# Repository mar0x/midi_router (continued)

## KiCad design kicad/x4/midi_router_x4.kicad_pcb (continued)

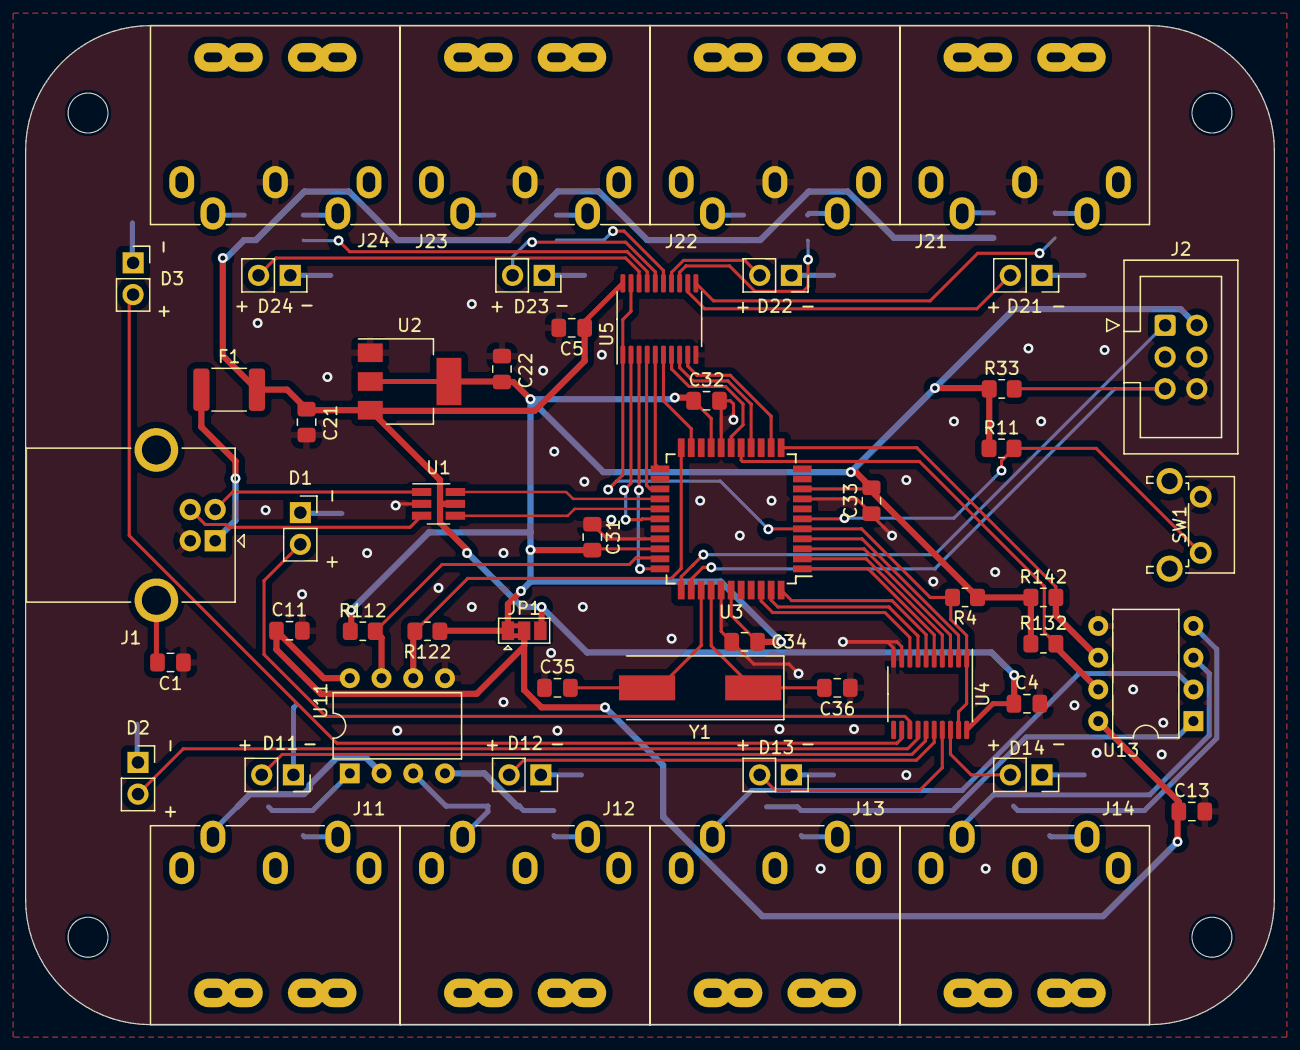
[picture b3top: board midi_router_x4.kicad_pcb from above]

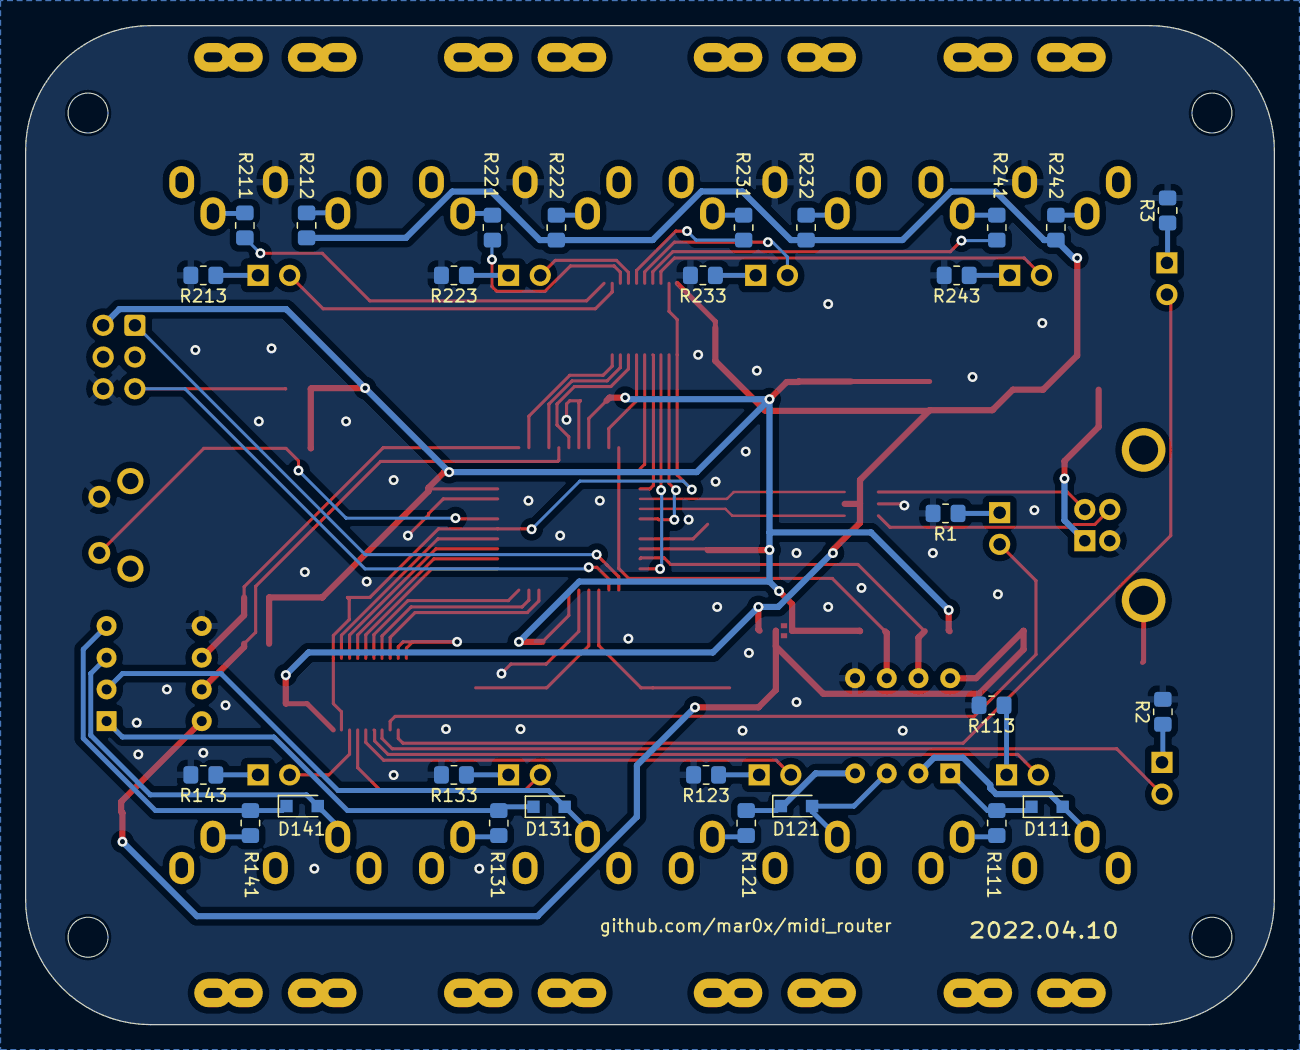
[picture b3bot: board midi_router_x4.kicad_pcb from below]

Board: 2 copper layers, 100.0 x 80.0 mm, 83 parts (27 on the bottom side), 81 nets.

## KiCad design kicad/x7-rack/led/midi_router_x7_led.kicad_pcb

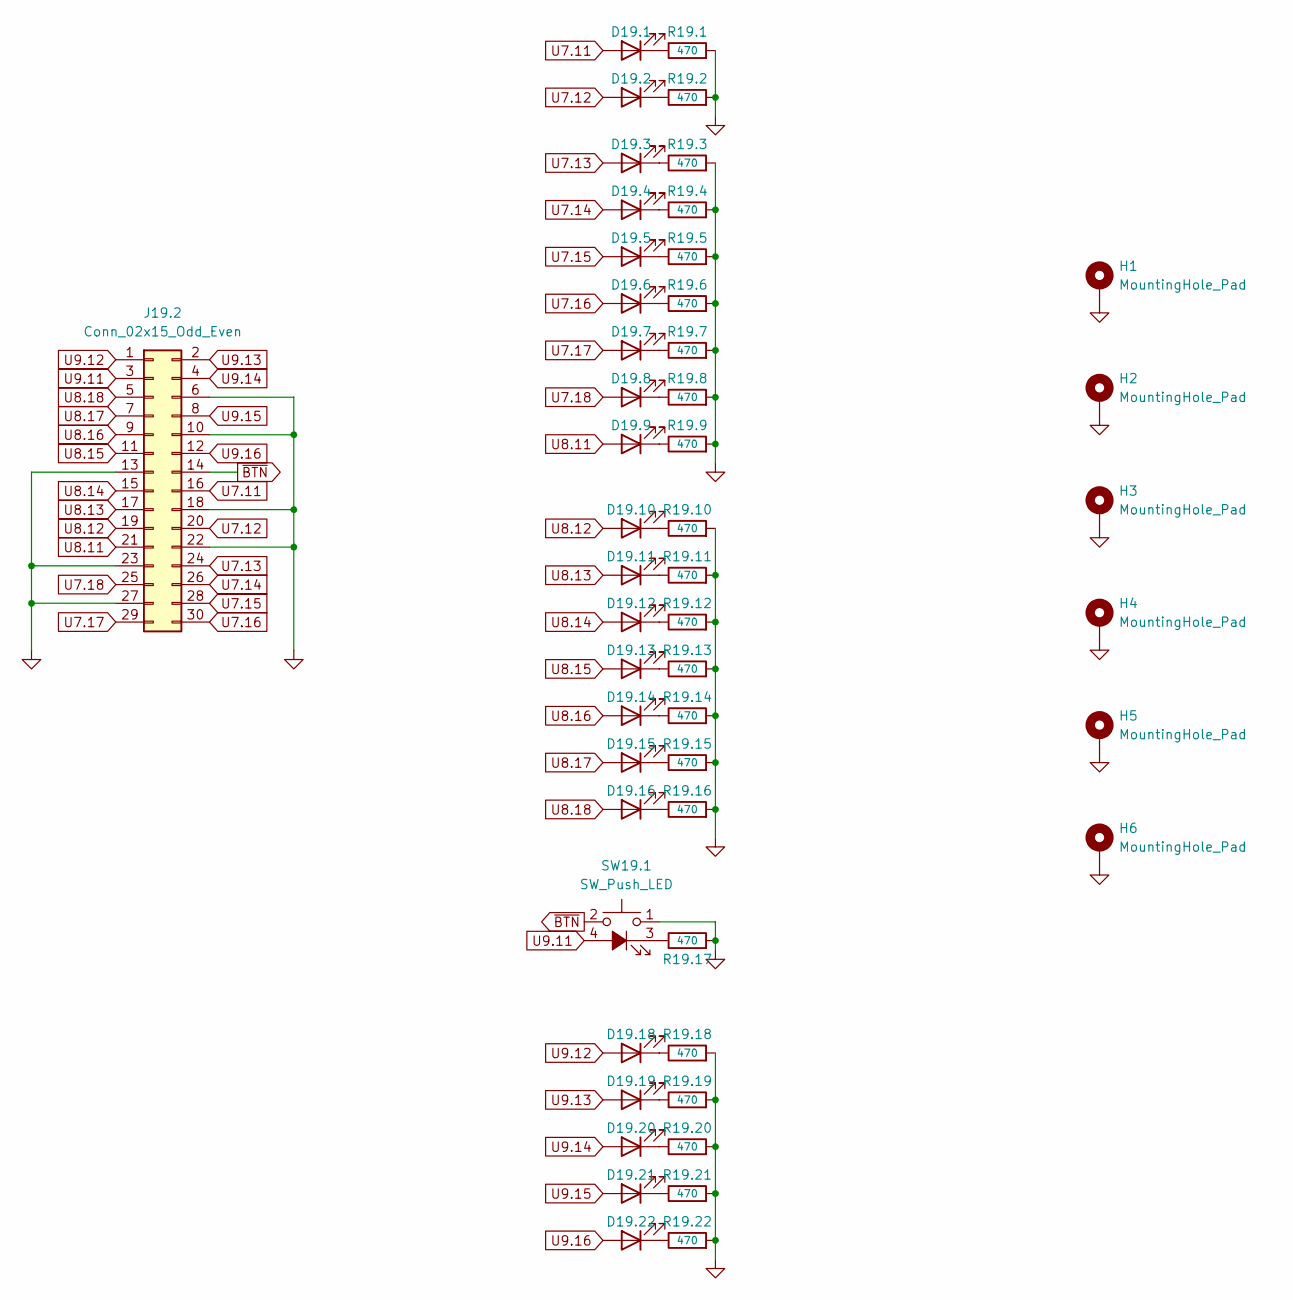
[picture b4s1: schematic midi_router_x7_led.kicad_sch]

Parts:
D19.1, D19.2, D19.3, D19.4, D19.5, D19.6, D19.7, D19.8, D19.9, D19.10, D19.11, D19.12, D19.13, D19.14, D19.15, D19.16, D19.18, D19.19, D19.20, D19.21, D19.22: LED; LED_Rectangular_W5.0mm_H2.0mm
H1, H2, H3, H4, H5, H6: MountingHole_Pad; MountingHole_3.2mm_M3_Pad_Via
J19.2: Conn_02x15_Odd_Even; IDC-Header_2x15_P2.54mm_Vertical
R19.1, R19.2, R19.3, R19.4, R19.5, R19.6, R19.7, R19.8, R19.9, R19.10, R19.11, R19.12, R19.13, R19.14, R19.15, R19.16, R19.17, R19.18, R19.19, R19.20, R19.21, R19.22: 470; R_0805_2012Metric
SW19.1: SW_Push_LED; SW_PUSH_6mm

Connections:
GND: H1.1, H2.1, H3.1, H4.1, H5.1, H6.1, J19.2.6, J19.2.10, J19.2.13, J19.2.18, J19.2.22, J19.2.23, J19.2.27, R19.1.2, R19.2.2, R19.3.2, R19.4.2, R19.5.2, R19.6.2, R19.7.2, R19.8.2, R19.9.2, R19.10.2, R19.11.2, R19.12.2, R19.13.2, R19.14.2, R19.15.2, R19.16.2, R19.17.2, R19.18.2, R19.19.2, R19.20.2, R19.21.2, R19.22.2, SW19.1.1
unnamed: D19.1.1 (K), R19.1.1
unnamed: D19.2.1 (K), R19.2.1
unnamed: D19.3.1 (K), R19.3.1
unnamed: D19.4.1 (K), R19.4.1
unnamed: D19.5.1 (K), R19.5.1
unnamed: D19.6.1 (K), R19.6.1
unnamed: D19.7.1 (K), R19.7.1
unnamed: D19.8.1 (K), R19.8.1
unnamed: D19.9.1 (K), R19.9.1
unnamed: D19.10.1 (K), R19.10.1
unnamed: D19.11.1 (K), R19.11.1
unnamed: D19.12.1 (K), R19.12.1
unnamed: D19.13.1 (K), R19.13.1
unnamed: D19.14.1 (K), R19.14.1
unnamed: D19.15.1 (K), R19.15.1
unnamed: D19.16.1 (K), R19.16.1
unnamed: D19.18.1 (K), R19.18.1
unnamed: D19.19.1 (K), R19.19.1
unnamed: D19.20.1 (K), R19.20.1
unnamed: D19.21.1 (K), R19.21.1
unnamed: D19.22.1 (K), R19.22.1
unnamed: R19.17.1, SW19.1.3 (K)
U7.11: D19.1.2 (A), J19.2.16
U7.12: D19.2.2 (A), J19.2.20
U7.13: D19.3.2 (A), J19.2.24
U7.14: D19.4.2 (A), J19.2.26
U7.15: D19.5.2 (A), J19.2.28
U7.16: D19.6.2 (A), J19.2.30
U7.17: D19.7.2 (A), J19.2.29
U7.18: D19.8.2 (A), J19.2.25
U8.11: D19.9.2 (A), J19.2.21
U8.12: D19.10.2 (A), J19.2.19
U8.13: D19.11.2 (A), J19.2.17
U8.14: D19.12.2 (A), J19.2.15
U8.15: D19.13.2 (A), J19.2.11
U8.16: D19.14.2 (A), J19.2.9
U8.17: D19.15.2 (A), J19.2.7
U8.18: D19.16.2 (A), J19.2.5
U9.11: J19.2.3, SW19.1.4 (A)
U9.12: D19.18.2 (A), J19.2.1
U9.13: D19.19.2 (A), J19.2.2
U9.14: D19.20.2 (A), J19.2.4
U9.15: D19.21.2 (A), J19.2.8
U9.16: D19.22.2 (A), J19.2.12
~BTN: J19.2.14, SW19.1.2

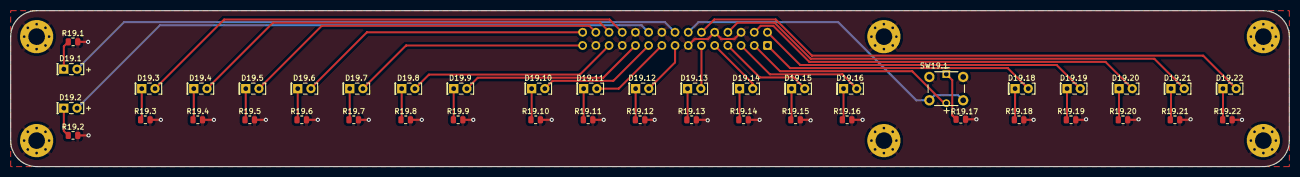
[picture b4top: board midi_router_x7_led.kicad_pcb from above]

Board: 2 copper layers, 246.0 x 30.0 mm, 51 parts (1 on the bottom side), 46 nets.

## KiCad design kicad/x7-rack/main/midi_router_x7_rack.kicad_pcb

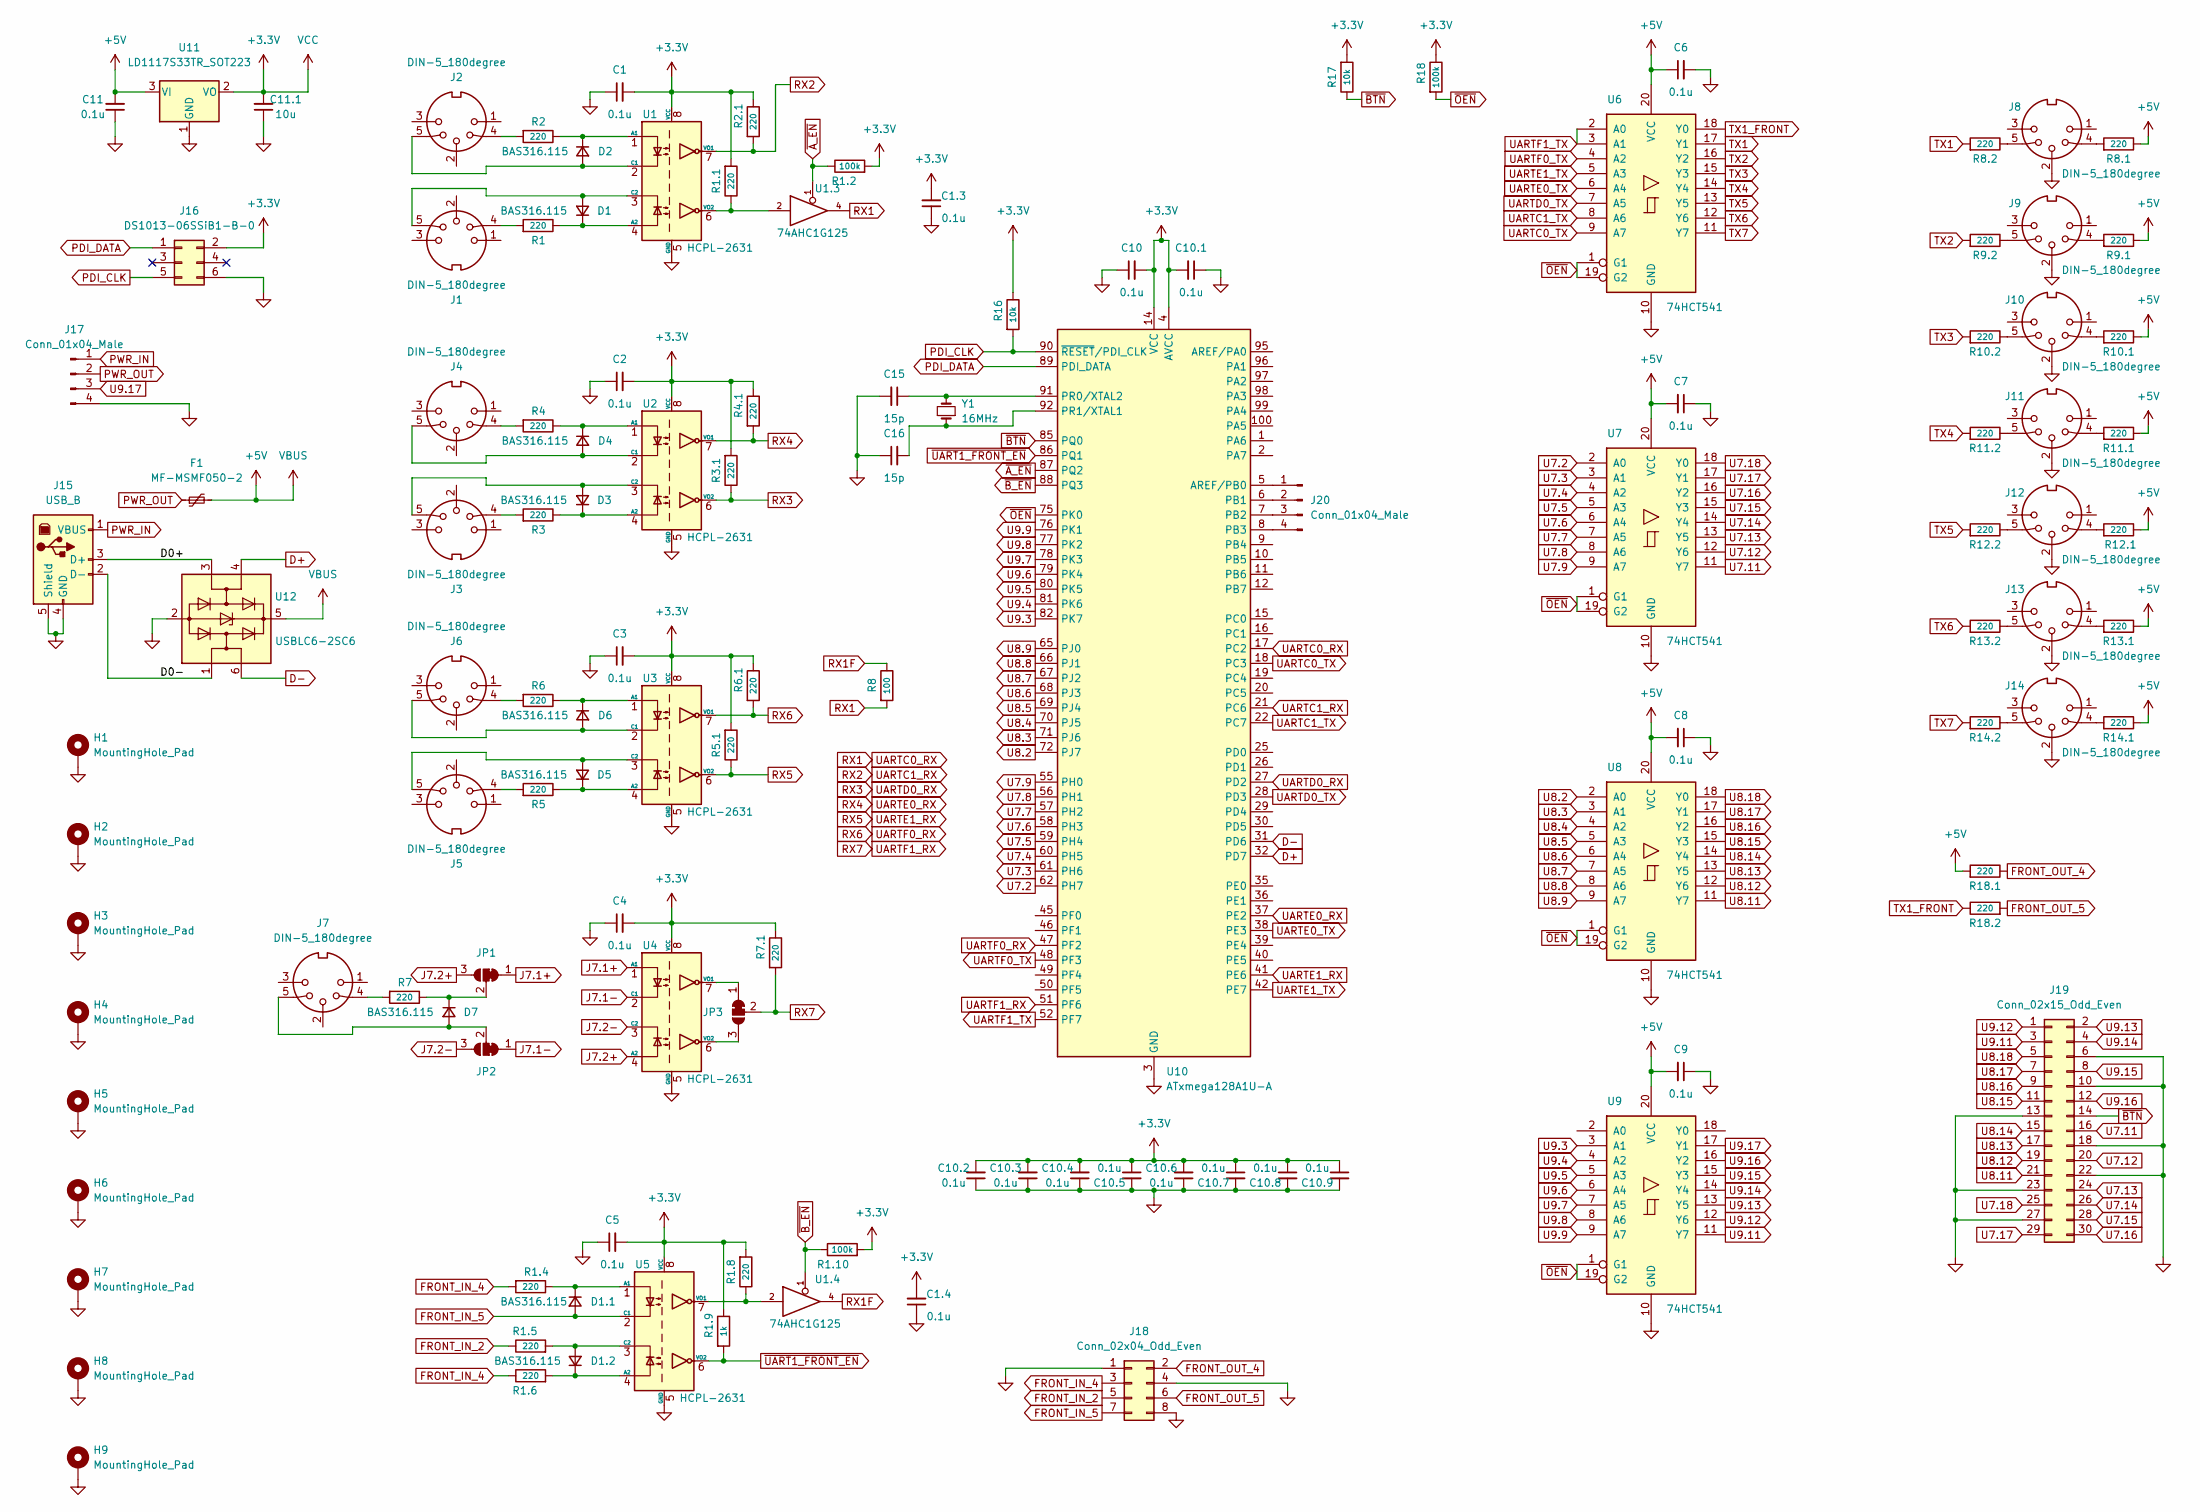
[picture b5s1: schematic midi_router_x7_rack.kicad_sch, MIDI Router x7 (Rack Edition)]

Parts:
C1, C1.3, C1.4, C2, C3, C4, C5, C6, C7, C8, C9, C10, C10.1, C10.2, C10.3, C10.4, C10.5, C10.6, C10.7, C10.8, C10.9, C11: 0.1u; C_0805_2012Metric
C11.1: 10u; C_0805_2012Metric
C15, C16: 15p; C_0805_2012Metric
D1, D1.1, D1.2, D2, D3, D4, D5, D6, D7: BAS316.115; D_SOD-323_HandSoldering
F1: MF-MSMF050-2; Fuse_1812_4532Metric
H1, H2, H3, H4, H5, H6, H7, H8, H9: MountingHole_Pad; MountingHole_3.2mm_M3_Pad_Via
J1, J2, J3, J4, J5, J6, J7, J8, J9, J10, J11, J12, J13, J14: DIN-5_180degree; DIN5MIDI-OOTDTY
J15: USB_B; USB_B_OST_USB-B1HSxx_Horizontal
J16: DS1013-06SSiB1-B-0; IDC-Header_2x03_P2.54mm_Vertical
J17: Conn_01x04_Male; JST_EH_B4B-EH-A_1x04_P2.50mm_Vertical
J18: Conn_02x04_Odd_Even; IDC-Header_2x04_P2.54mm_Vertical
J19: Conn_02x15_Odd_Even; IDC-Header_2x15_P2.54mm_Vertical
J20: Conn_01x04_Male; PinHeader_1x04_P2.54mm_Vertical
JP1, JP2, JP3: SolderJumper_3_Bridged12; SolderJumper-3_P1.3mm_Bridged12_RoundedPad1.0x1.5mm_NumberL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
R1, R1.1, R1.4, R1.5, R1.6, R1.8, R2, R2.1, R3, R3.1, R4, R4.1, R5, R5.1, R6, R6.1, R7, R7.1, R8.1, R8.2, R9.1, R9.2, R10.1, R10.2, R11.1, R11.2, R12.1, R12.2, R13.1, R13.2, R14.1, R14.2, R18.1, R18.2: 220; R_0805_2012Metric
R1.2, R1.10, R18: 100k; R_0805_2012Metric
R1.9: 1k; R_0805_2012Metric
R8: 100; R_0805_2012Metric
R16, R17: 10k; R_0805_2012Metric
U1, U2, U3, U4, U5: HCPL-2631; DIP-8_W7.62mm
U1.3, U1.4: 74AHC1G125; SOT-23-5
U6, U7, U8, U9: 74HCT541; TSSOP-20_4.4x6.5mm_P0.65mm
U10: ATxmega128A1U-A; TQFP-100_14x14mm_P0.5mm
U11: LD1117S33TR_SOT223; SOT-223-3_TabPin2
U12: USBLC6-2SC6; SOT-23-6
Y1: 16MHz; Crystal_SMD_HC49-SD

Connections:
+3V3: C1.2, C1.3.2, C1.4.2, C2.2, C3.2, C4.2, C5.2, C10.2, C10.1.2, C10.2.2, C10.3.2, C10.4.2, C10.5.1, C10.6.2, C10.7.1, C10.8.1, C10.9.1, C11.1.2, J16.2, R1.1.2, R1.2.2, R1.8.2, R1.9.1, R1.10.2, R2.1.1, R3.1.2, R4.1.1, R5.1.2, R6.1.1, R7.1.1, R16.1, R17.2, R18.1, U1.8 (VCC), U1.3.5 (VCC), U1.4.5 (VCC), U2.8 (VCC), U3.8 (VCC), U4.8 (VCC), U5.8 (VCC), U10.4 (AVCC), U10.14 (VCC), U10.24 (VCC), U10.34 (VCC), U10.44 (VCC), U10.54 (VCC), U10.64 (VCC), U10.74 (VCC), U10.83 (VCC), U10.94 (AVCC), U11.2 (VO)
+5V: C6.1, C7.2, C8.2, C9.2, C11.2, F1.2, R8.1.1, R9.1.1, R10.1.1, R11.1.1, R12.1.1, R13.1.1, R14.1.1, R18.1.2, U6.20 (VCC), U7.20 (VCC), U8.20 (VCC), U9.20 (VCC), U11.3 (VI), U12.5 (VBUS)
/D0+: J15.3 (D+), U12.3 (I/O2)
/D0-: J15.2 (D-), U12.1 (I/O1)
D+: U10.32 (PD7), U12.4 (I/O2)
D-: U10.31 (PD6), U12.6 (I/O1)
FRONT_IN_2: J18.5, R1.5.1
FRONT_IN_4: J18.3, R1.4.2, R1.6.1
FRONT_IN_5: D1.1.2 (A), J18.7, U5.2 (C1)
FRONT_OUT_4: J18.2, R18.1.1
FRONT_OUT_5: J18.6, R18.2.2
GND: C1.1, C1.3.1, C1.4.1, C2.1, C3.1, C4.1, C5.1, C6.2, C7.1, C8.1, C9.1, C10.1, C10.1.1, C10.2.1, C10.3.1, C10.4.1, C10.5.2, C10.6.1, C10.7.2, C10.8.2, C10.9.2, C11.1, C11.1.1, C15.2, C16.1, H1.1, H2.1, H3.1, H4.1, H5.1, H6.1, H7.1, H8.1, H9.1, J8.2, J9.2, J10.2, J11.2, J12.2, J13.2, J14.2, J15.4 (GND), J15.5 (Shield), J16.6, J17.4, J18.1, J18.4, J18.8, J19.6, J19.10, J19.13, J19.18, J19.22, J19.23, J19.27, U1.5 (GND), U1.3.3 (GND), U1.4.3 (GND), U2.5 (GND), U3.5 (GND), U4.5 (GND), U5.5 (GND), U6.10 (GND), U7.10 (GND), U8.10 (GND), U9.10 (GND), U10.3 (GND), U10.13 (GND), U10.23 (GND), U10.33 (GND), U10.43 (GND), U10.53 (GND), U10.63 (GND), U10.73 (GND), U10.84 (GND), U10.93 (GND), U11.1 (GND), U12.2 (GND)
J7.1+: JP1.1 (A), U4.1 (A1)
J7.1-: JP2.1 (A), U4.2 (C1)
J7.2+: JP1.3 (B), U4.4 (A2)
J7.2-: JP2.3 (B), U4.3 (C2)
unnamed: D1.2 (A), J1.5, U1.3 (C2)
unnamed: D1.1 (K), R1.1, U1.4 (A2)
unnamed: D1.1.1 (K), R1.4.1, U5.1 (A1)
unnamed: D1.2.2 (A), R1.5.2, U5.3 (C2)
unnamed: D1.2.1 (K), R1.6.2, U5.4 (A2)
unnamed: D2.2 (A), J2.5, U1.2 (C1)
unnamed: D2.1 (K), R2.1, U1.1 (A1)
unnamed: D3.2 (A), J3.5, U2.3 (C2)
unnamed: D3.1 (K), R3.1, U2.4 (A2)
unnamed: D4.2 (A), J4.5, U2.2 (C1)
unnamed: D4.1 (K), R4.1, U2.1 (A1)
unnamed: D5.2 (A), J5.5, U3.3 (C2)
unnamed: D5.1 (K), R5.1, U3.4 (A2)
unnamed: D6.2 (A), J6.5, U3.2 (C1)
unnamed: D6.1 (K), R6.1, U3.1 (A1)
unnamed: D7.2 (A), J7.5, JP2.2 (C)
unnamed: D7.1 (K), JP1.2 (C), R7.1
unnamed: J1.4, R1.2
unnamed: J2.4, R2.2
unnamed: J3.4, R3.2
unnamed: J4.4, R4.2
unnamed: J5.4, R5.2
unnamed: J6.4, R6.2
unnamed: J7.4, R7.2
unnamed: J8.4, R8.1.2
unnamed: J8.5, R8.2.1
unnamed: J9.4, R9.1.2
unnamed: J9.5, R9.2.1
unnamed: J10.4, R10.1.2
unnamed: J10.5, R10.2.1
unnamed: J11.4, R11.1.2
unnamed: J11.5, R11.2.1
unnamed: J12.4, R12.1.2
unnamed: J12.5, R12.2.1
unnamed: J13.4, R13.1.2
unnamed: J13.5, R13.2.1
unnamed: J14.4, R14.1.2
unnamed: J14.5, R14.2.1
unnamed: J20.1, U10.5 (AREF/PB0)
unnamed: J20.2, U10.6 (PB1)
unnamed: J20.3, U10.7 (PB2)
unnamed: J20.4, U10.8 (PB3)
unnamed: JP3.1 (A), U4.7 (VO1)
unnamed: JP3.3 (B), U4.6 (VO2)
unnamed: R1.1.1, U1.6 (VO2), U1.3.2
unnamed: R1.8.1, U1.4.2, U5.7 (VO1)
unnamed: C15.1, U10.91 (PR0/XTAL2), Y1.2
unnamed: C16.2, U10.92 (PR1/XTAL1), Y1.1
PDI_CLK: J16.5, R16.2, U10.90 (~RESET/PDI_CLK)
PDI_DATA: J16.1, U10.89 (PDI_DATA)
PWR_IN: J15.1 (VBUS), J17.1
PWR_OUT: F1.1, J17.2
RX1: R8.2, U1.3.4, U10.17 (PC2)
RX1F: R8.1, U1.4.4
RX2: R2.1.2, U1.7 (VO1), U10.21 (PC6)
RX3: R3.1.1, U2.6 (VO2), U10.27 (PD2)
RX4: R4.1.2, U2.7 (VO1), U10.37 (PE2)
RX5: R5.1.1, U3.6 (VO2), U10.41 (PE6)
RX6: R6.1.2, U3.7 (VO1), U10.47 (PF2)
RX7: JP3.2 (C), R7.1.2, U10.51 (PF6)
TX1: R8.2.2, U6.17 (Y1)
TX1_FRONT: R18.2.1, U6.18 (Y0)
TX2: R9.2.2, U6.16 (Y2)
TX3: R10.2.2, U6.15 (Y3)
TX4: R11.2.2, U6.14 (Y4)
TX5: R12.2.2, U6.13 (Y5)
TX6: R13.2.2, U6.12 (Y6)
TX7: R14.2.2, U6.11 (Y7)
U7.2: U7.2 (A0), U10.62 (PH7)
U7.3: U7.3 (A1), U10.61 (PH6)
U7.4: U7.4 (A2), U10.60 (PH5)
U7.5: U7.5 (A3), U10.59 (PH4)
U7.6: U7.6 (A4), U10.58 (PH3)
U7.7: U7.7 (A5), U10.57 (PH2)
U7.8: U7.8 (A6), U10.56 (PH1)
U7.9: U7.9 (A7), U10.55 (PH0)
U7.11: J19.16, U7.11 (Y7)
U7.12: J19.20, U7.12 (Y6)
U7.13: J19.24, U7.13 (Y5)
U7.14: J19.26, U7.14 (Y4)
U7.15: J19.28, U7.15 (Y3)
U7.16: J19.30, U7.16 (Y2)
U7.17: J19.29, U7.17 (Y1)
U7.18: J19.25, U7.18 (Y0)
U8.2: U8.2 (A0), U10.72 (PJ7)
U8.3: U8.3 (A1), U10.71 (PJ6)
U8.4: U8.4 (A2), U10.70 (PJ5)
U8.5: U8.5 (A3), U10.69 (PJ4)
U8.6: U8.6 (A4), U10.68 (PJ3)
U8.7: U8.7 (A5), U10.67 (PJ2)
U8.8: U8.8 (A6), U10.66 (PJ1)
U8.9: U8.9 (A7), U10.65 (PJ0)
U8.11: J19.21, U8.11 (Y7)
U8.12: J19.19, U8.12 (Y6)
U8.13: J19.17, U8.13 (Y5)
U8.14: J19.15, U8.14 (Y4)
U8.15: J19.11, U8.15 (Y3)
U8.16: J19.9, U8.16 (Y2)
U8.17: J19.7, U8.17 (Y1)
U8.18: J19.5, U8.18 (Y0)
U9.3: U9.3 (A1), U10.82 (PK7)
U9.4: U9.4 (A2), U10.81 (PK6)
U9.5: U9.5 (A3), U10.80 (PK5)
U9.6: U9.6 (A4), U10.79 (PK4)
U9.7: U9.7 (A5), U10.78 (PK3)
U9.8: U9.8 (A6), U10.77 (PK2)
U9.9: U9.9 (A7), U10.76 (PK1)
U9.11: J19.3, U9.11 (Y7)
U9.12: J19.1, U9.12 (Y6)
U9.13: J19.2, U9.13 (Y5)
U9.14: J19.4, U9.14 (Y4)
U9.15: J19.8, U9.15 (Y3)
U9.16: J19.12, U9.16 (Y2)
U9.17: J17.3, U9.17 (Y1)
UARTC0_TX: U6.9 (A7), U10.18 (PC3)
UARTC1_TX: U6.8 (A6), U10.22 (PC7)
UARTD0_TX: U6.7 (A5), U10.28 (PD3)
UARTE0_TX: U6.6 (A4), U10.38 (PE3)
UARTE1_TX: U6.5 (A3), U10.42 (PE7)
UARTF0_TX: U6.4 (A2), U10.48 (PF3)
UARTF1_TX: U6.2 (A0), U6.3 (A1), U10.52 (PF7)
~A_EN: R1.2.1, U1.3.1, U10.87 (PQ2)
~BTN: J19.14, R17.1, U10.85 (PQ0)
~B_EN: R1.10.1, U1.4.1, U10.88 (PQ3)
~OEN: R18.2, U6.1 (G1), U6.19 (G2), U7.1 (G1), U7.19 (G2), U8.1 (G1), U8.19 (G2), U9.1 (G1), U9.19 (G2), U10.75 (PK0)
~UART1_FRONT_EN: R1.9.2, U5.6 (VO2), U10.86 (PQ1)

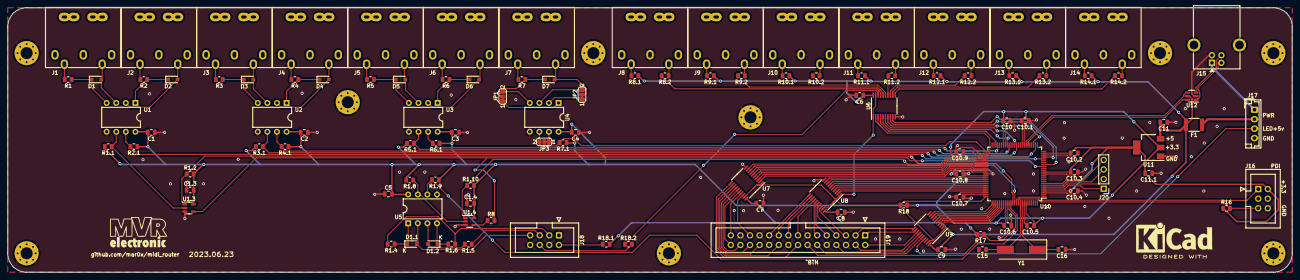
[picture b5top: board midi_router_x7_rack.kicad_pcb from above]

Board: 2 copper layers, 340.0 x 70.0 mm, 123 parts (0 on the bottom side), 142 nets.

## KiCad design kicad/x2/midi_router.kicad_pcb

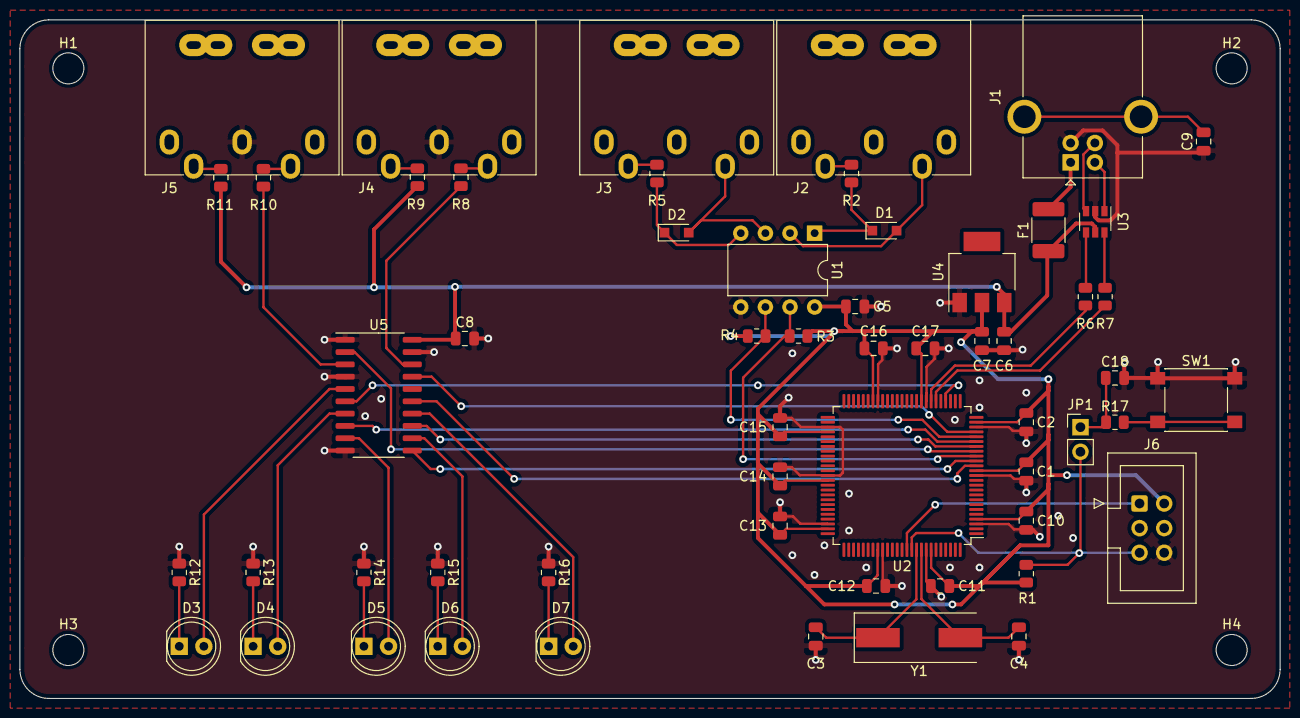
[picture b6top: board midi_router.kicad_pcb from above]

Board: 2 copper layers, 130.0 x 70.0 mm, 61 parts (0 on the bottom side), 48 nets.

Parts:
C1, C2, C5, C6, C8, C10, C11, C12, C13, C14, C15, C16, C17, C18: 0.1u; C_0805_2012Metric
C3, C4: 15p; C_0805_2012Metric
C7: 10u; C_0805_2012Metric
C9: 0.01u; C_0805_2012Metric
D1, D2: D; D_SOD-323_HandSoldering
D3, D4, D5, D6, D7: LED; LED_D5.0mm
F1: MF-MSMF050-2; Fuse_1812_4532Metric_Castellated
H1, H2, H3, H4: MountingHole; MountingHole_3.2mm_M3
J1: USB_B; USB_B_OST_USB-B1HSxx_Horizontal
J2, J3, J4, J5: DIN-5_180degree; DIN5MIDI-OOTDTY
J6: Conn_02x03_Odd_Even; IDC-Header_2x03_P2.54mm_Vertical
JP1: Jumper_NO_Small; PinHeader_1x02_P2.54mm_Vertical
R1: 10k; R_0805_2012Metric
R2, R5, R8, R9, R10, R11: 220; R_0805_2012Metric
R3, R4: 470; R_0805_2012Metric
R6, R7: 22; R_0805_2012Metric
R12, R13, R14, R15, R16: 1k; R_0805_2012Metric
R17: 100; R_0805_2012Metric
SW1: SW_Push; SW_Push_1P1T_NO_6x6mm_H9.5mm
U1: HCPL2730; DIP-8_W7.62mm
U2: ATxmega128A1U-AU; TQFP-100_14x14mm_P0.5mm
U3: USBLC6-2SC6; SOT-23-6
U4: LD1117S33TR_SOT223; SOT-223-3_TabPin2
U5: 74HC244; SO-20_5.3x12.6mm_P1.27mm
Y1: 16MHz; Crystal_SMD_HC49-SD

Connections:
+3V3: C1.2, C2.1, C5.1, C7.1, C10.1, C11.1, C12.1, C13.1, C14.1, C15.1, C16.1, C17.1, J6.2, R1.1, R3.1, R4.1, U1.8, U2.4, U2.14, U2.24, U2.34, U2.44, U2.54, U2.64, U2.74, U2.83, U2.94, U4.2
+5V: C6.1, C8.1, F1.1, R9.1, R11.1, U3.5, U4.3, U5.20
D+: R6.1, U2.32
D-: R7.1, U2.31
GND: C1.1, C2.2, C3.1, C4.1, C5.2, C6.2, C7.2, C8.2, C9.1, C10.2, C11.2, C12.2, C13.2, C14.2, C15.2, C16.2, C17.2, C18.2, J1.4, J4.2, J5.2, J6.6, R12.1, R13.1, R14.1, R15.1, R16.1, SW1.1, U1.5, U2.3, U2.13, U2.23, U2.33, U2.43, U2.53, U2.63, U2.73, U2.84, U2.93, U3.2, U4.1, U5.1, U5.4, U5.10, U5.19
unnamed: C3.2, U2.91, Y1.1
unnamed: C4.2, U2.92, Y1.2
unnamed: C9.2, J1.5
unnamed: C18.1, JP1.1, R17.1
unnamed: D1.1, R2.2, U1.1
unnamed: D1.2, J2.5, U1.2
unnamed: D2.1, R5.2, U1.4
unnamed: D2.2, J3.5, U1.3
unnamed: D3.1, R12.2
unnamed: D3.2, U5.5
unnamed: D4.1, R13.2
unnamed: D4.2, U5.7
unnamed: D5.1, R14.2
unnamed: D5.2, U5.9
unnamed: D6.1, R15.2
unnamed: D6.2, U5.12
unnamed: D7.1, R16.2
unnamed: D7.2, U5.14
unnamed: F1.2, J1.1
unnamed: J1.2, U3.1
unnamed: J1.3, U3.3
unnamed: J2.4, R2.1
unnamed: J3.4, R5.1
unnamed: J4.4, R9.2
unnamed: J4.5, R8.1
unnamed: J5.4, R11.2
unnamed: J5.5, R10.1
unnamed: R6.2, U3.4
unnamed: R7.2, U3.6
unnamed: R8.2, U5.18
unnamed: R10.2, U5.3
unnamed: R17.2, SW1.2
PDI_CLK: J6.5, JP1.2, R1.2, U2.90
PDI_DATA: J6.1, U2.89
UARTC_RXD0: R3.2, U1.7, U2.17
UARTC_RXD1: R4.2, U1.6, U2.21
UARTC_SRX0: U2.15, U5.15
UARTC_SRX1: U2.19, U5.13
UARTC_STX0: U2.16, U5.11
UARTC_STX1: U2.20, U5.8
UARTC_TXD0: U2.18, U5.2
UARTC_TXD1: U2.22, U5.17
UARTD_SUSB: U2.29, U5.6

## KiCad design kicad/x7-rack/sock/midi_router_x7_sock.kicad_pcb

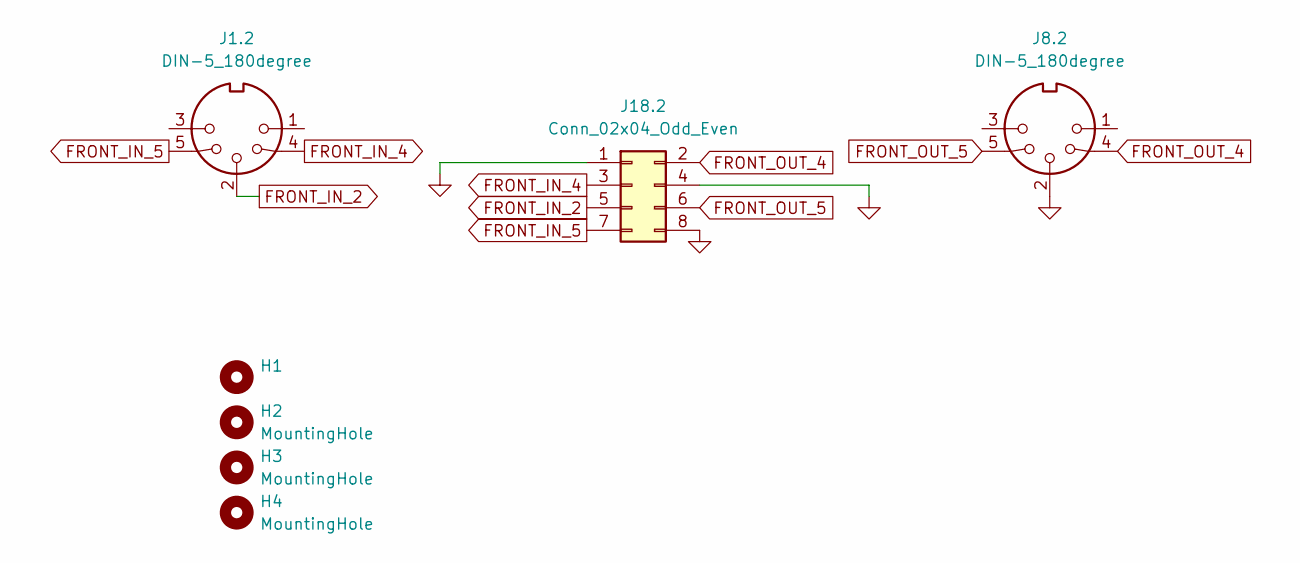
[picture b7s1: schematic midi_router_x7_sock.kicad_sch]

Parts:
H1: (no value)
H2, H3, H4: MountingHole; MountingHole_3.2mm_M3
J1.2, J8.2: DIN-5_180degree; DIN5MIDI-OOTDTY
J18.2: Conn_02x04_Odd_Even; IDC-Header_2x04_P2.54mm_Vertical

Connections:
FRONT_IN_2: J1.2.2, J18.2.5
FRONT_IN_4: J1.2.4, J18.2.3
FRONT_IN_5: J1.2.5, J18.2.7
FRONT_OUT_4: J8.2.4, J18.2.2
FRONT_OUT_5: J8.2.5, J18.2.6
GND: J8.2.2, J18.2.1, J18.2.4, J18.2.8

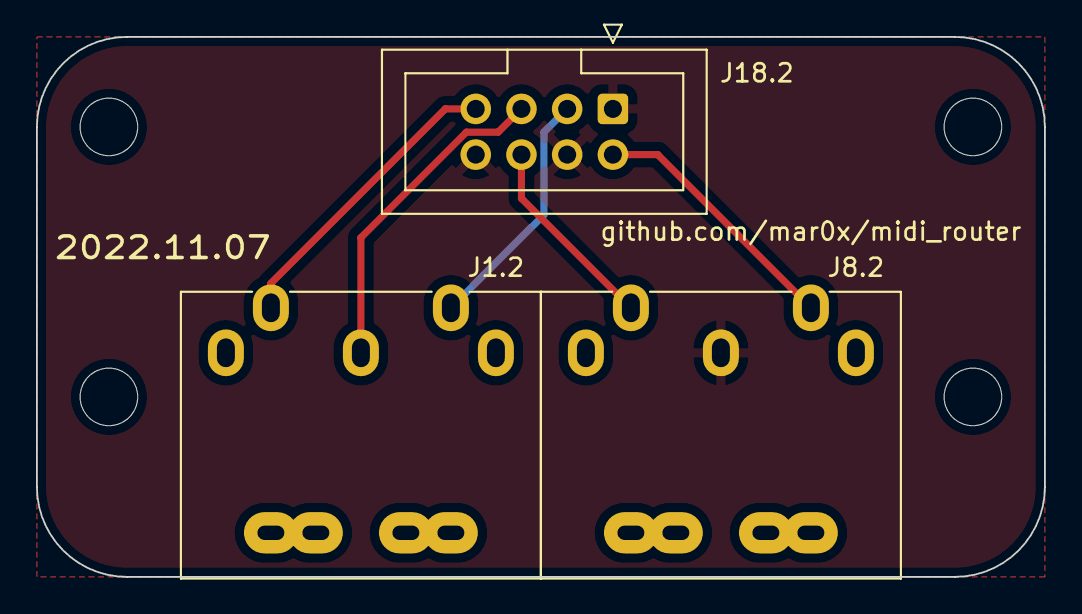
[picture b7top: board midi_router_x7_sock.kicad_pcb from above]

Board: 2 copper layers, 56.0 x 30.0 mm, 7 parts (0 on the bottom side), 6 nets.

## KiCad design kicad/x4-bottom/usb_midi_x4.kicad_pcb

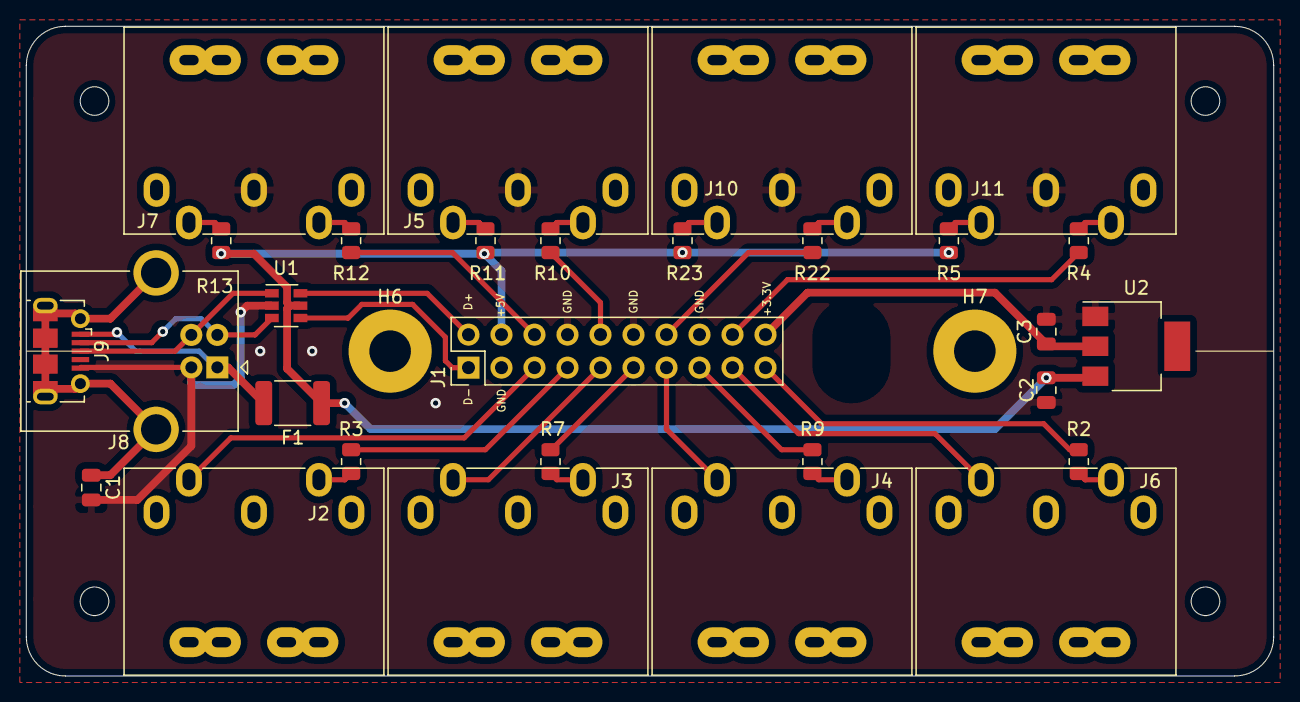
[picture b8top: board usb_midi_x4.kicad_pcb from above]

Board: 2 copper layers, 96.0 x 50.0 mm, 35 parts (0 on the bottom side), 33 nets.

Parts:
C1: 10nF; C_0805_2012Metric
C2: 0.1u; C_0805_2012Metric
C3: 10u; C_0805_2012Metric
F1: MF-MSMF050-2; Fuse_1812_4532Metric_Pad1.30x3.40mm_HandSolder
H1, H2, H3, H4: MountingHole; MountingHole_2.2mm_M2_ISO7380
H6, H7: MountingHole; MountingHole_3.2mm_M3_Pad
J1: Conn_02x10_Odd_Even; PinHeader_2x10_P2.54mm_Vertical
J2, J3, J4, J5, J6, J7, J10, J11: DIN-5_180degree; DIN5MIDI-OOTDTY
J8: DS1099; USB_B_OST_USB-B1HSxx_Horizontal
J9: DS1099; USB_Micro-B_Molex-105017-0001
R2, R3, R4, R5, R7, R9, R10, R11, R12, R13, R22, R23: 220; R_0805_2012Metric
U1: USBLC6-2SC6; SOT-23-6
U2: LD1117S33TR_SOT223; SOT-223-3_TabPin2

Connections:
+3V3: C3.1, J1.20, U2.2
+5V: C2.1, F1.1, J1.4, R5.1, R11.1, R13.1, R23.1, U1.5, U2.3
D+: J8.3, J9.3, U1.1
D-: J8.2, J9.2, U1.3
GND: C1.2, C2.2, C3.2, J1.3, J1.8, J1.12, J1.16, J5.2, J7.2, J8.4, J9.5, J10.2, J11.2, U1.2, U2.1
IN1_5V: J1.7, R3.1
IN1_D: J1.5, J2.5
IN2_5V: J1.11, R7.1
IN2_D: J1.9, J3.5
IN3_5V: J1.15, R9.1
IN3_D: J1.13, J4.5
IN4_5V: J1.19, R2.1
IN4_D: J1.17, J6.5
unnamed: J2.4, R3.2
unnamed: J3.4, R7.2
unnamed: J4.4, R9.2
unnamed: J5.4, R11.2
unnamed: J5.5, R10.1
unnamed: J6.4, R2.2
unnamed: J7.4, R13.2
unnamed: J7.5, R12.1
unnamed: J10.4, R23.2
unnamed: J10.5, R22.1
unnamed: J11.4, R5.2
unnamed: J11.5, R4.1
OD+: J1.2, U1.6
OD-: J1.1, U1.4
OUT1: J1.18, R4.2
OUT2: J1.14, R22.2
OUT3: J1.10, R10.2
OUT4: J1.6, R12.2
SHLD: C1.1, J8.5, J9.6
VBUS: F1.2, J8.1, J9.1

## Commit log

2021-07-27 USB MIDI Router.
    AVR xmega based device to add multiple "classic" MIDI ports in PC via USB.
2021-07-27 x2 prototype: fixing MIDI out connection.
2021-07-27 x7: updating MIDI connector 3D model.
2021-07-29 Minor tracing fixes.
2021-10-21 Changed files format only.
2021-10-21 Upgrading IAR projects.
2021-10-21 Bootloaders adjusted to boards and MCUs.
2021-10-21 Tweaking x4 box.
2021-10-21 Missing dummy_board added.
2021-10-21 Fixed bootloaders.
2021-10-21 Binary DFU bootloaders.
2021-10-21 Adjust DFU binary name.
2021-10-21 Make target to upload DFU bootloader.
2021-10-21 Enable drivers.
2021-10-22 Fixing various misprints.
2021-11-03 Makefiles rework.
2021-11-11 Makefiles fixed once again.
2021-11-13 Box improvements.
    - fixed error (0.5mm) in board position calculation;
    - removed bottom enforcement;
    - parametric led shape;
2021-11-13 Updating BOM.
2021-11-13 Timer interrupt level changed to MEDIUM to avoid splitter delays.
2021-11-13 Store and restore flags in pin change interrupts.
2021-11-13 Initial serial control implementation.
2021-12-04 Changing timer interrupt level once again.
2021-12-04 Reducing copy-n-paste lines number.
2021-12-08 Using avrdude from path.
2021-12-08 Updating manufacture name.
2021-12-08 Improving performance.
    - introducing stats;
    - removing serial RX buffers;
    - tweaking leds;
2021-12-09 Target to copy firmware to bin.
2021-12-09 Introducing tests.
2021-12-10 Fixing compiler warnings.
2021-12-10 FW 2021.12.10
2021-12-10 Updating USB transfer error count.
2021-12-11 Adding rst button hole.
2021-12-28 Fixing MIDI command extraction.
    For some SysEx data command() may return non-zero which lead to skip
    MIDI event by USB stack. Affects only MIDI->USB data pass.
2021-12-28 Updating components.
2021-12-28 FW 2021.12.28
2022-01-09 Uploading HW revision.
2022-03-13 Introducing Splitter 1x6 box.
    Minor box improvements.
2022-03-13 Updating BOM and router schemas.
2022-03-22 Adjusting x2 led output.
2022-03-22 Introducing tx_traits.
2022-03-28 Introducing test modes.
2022-03-28 Updating firmware version.
2022-03-29 Minor tweaks.
2022-04-10 Updating MIDI socket 3D model.
2022-04-10 Introducing x4 flat board.
2022-05-10 Introducing x4-flat dfu, firmware, and box.
2022-07-15 4x4 flat: fixing incoming port for spliiter mode.
2022-07-15 4x4-flat: making box 4mm lower.
2022-07-28 Making box 1mm lower.
2022-07-30 Double splitter.
    Introducing midi::tx_sent mask and intications.
2022-08-10 Experimental changes
    Merge & split 4->4 mode.
2022-08-13 Making state static.
    This helps compiler to produce more compact (and fast) code.
    Incoming port queue size increased to 32 bytes to transfer more messages
    before overflow occurs.
2022-08-15 Introducing cdc_print_hex().
2022-08-15 Fixing port id in DRE interrupt function.
2022-08-20 Avoid racing conditions in timer handlers.
2022-08-20 Using loop to reset stat data.
2022-08-20 Code size optimization.
    Replacing case with table.
2022-08-20 Introducing mode change commands.
2022-08-20 Calculating bitmask for port list DRE usage.
2022-08-20 Various fixes.
    - DRE stuck: process queue until DRE mask is non zero.
    - DRE last port stuck: avoid racing with tx_ring_non_empty_mask().
    While first port data is written and put into the queue, last port have
    more time to send previous frame and not require DRE interrupt.
    - timeout processing fixes: timeout action can be performed only when
    DRE mask is 0 (e.g. not pending write operations).
2022-08-20 Mode change commands implementation.
2022-08-20 Ring at() operation.
2022-08-20 Firmware 2022.08.19Ex.
2022-08-23 7x7: making box 5mm lower.
2022-09-22 Merger and bit splitter introduced.
2022-09-26 Splitting MIDI_IN and MIDI_OUT count.
2022-09-26 Introducing MIDI command serial ID.
    For command indexing purposes each command associated with serial ID.
2022-09-26 Reconstructing skipped MIDI command.
    Yamaha MM6 and Alesis SR16 send non-standard MIDI flow: "Note ON" command
    with parameters usually not followed by "Note OFF". Instead only paramaters
    are send. Router trued to re-construct the complete messages for further
    merging and processing.
2022-09-26 Added filter for IN1 as requested.
2022-09-26 Complete MIDI flow mock.
2022-09-26 FW-2022.09.25Ex
2022-11-01 Introducing command normalizer.
    Normalizer aimed to restore the MIDI command "optimized" by some
    MIDI keyboards (notable "Samson Carbon 61", "Yamaha MM6").
    Where "optimize" means skip the MIDI command "Note On" or "Note Off"
    byte and send only it's parameters.
    "Samson Carbon 61" optimizes only frequently repeating events while
    "Yamaha MM6" do it more "aggresively".
2022-11-01 Take one
2022-11-04 FW-2022.11.04Ex
    Splitter mode changes.
    Controlling port #1 state via CC20 for port #3.
    Port #1 disabled by default.
    Input port #1, #2, #3 data are merged to output port #1.
    Input port #4 data duplicated (splitted) to ports #2, #3, #4.
2022-11-05 FW-2022.11.05Ex
    Port0 default active.
2022-11-08 Introducing MIDI Router x7 Rack.
    Schematic and PCBs.
2022-11-08 Rack case front and back drawings.
2022-11-08 MIDI Router x7 firmware template.
2022-11-23 Start working on Note->CC convertor
2022-11-23 Accidental changes
2022-11-23 Illustrator files added
2022-11-26 Introducing Note2CC.
2022-11-26 Fixing DRE processing
2022-11-27 Updating rack panels.
2022-11-27 Fixing key mapping and NoteOff handle
    Some MIDI keyboards send NoteOn,Tone,0 instead of NoteOff,Tone,0.
2022-11-28 Adding some routing
2022-11-29 Note2CC with routing
2022-12-24 MIDI Router x7 Rack bootloader and hw
2022-12-27 Add Bio Data convertor
    MIDI Sprout source connected to Note2CC convertor schema
    https://github.com/electricityforprogress/MIDIsprout
2023-01-03 MIDI Router x7 Rack: fixing pin mapping
2023-02-03 MIDI Router x7 Rack: enabling mode indicators
2023-02-03 FW 2023.02.03
2023-06-23 Fixing main board issues
    - box to ground connection
    - RX1 connection
2023-06-23 Updating KiCAD
2023-06-23 Adding Atmel-ICE programmer
2023-07-06 Sync state with LED
2024-03-19 Add download target
2024-05-25 Download target cusomization
    Use DL_EXT and DL_DIR variables
2024-06-15 Add atxmega32a4u mini board
2024-06-15 Updating .gitignore
2024-06-15 Version update
2024-06-15 x4 KiCad upgrade
2024-06-15 x7 KiCad upgrade
2024-06-15 x4-top KiCad upgrade
2024-06-15 Providing INF file
    This INF file should help Windows 7,8 users to enable MIDI Router
    serial port.
    Thanks to @iflyhigh .
    This close #1 issue (sad but true).
